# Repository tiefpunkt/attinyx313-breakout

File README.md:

# ATtiny x2313 Breakout Board

Want to try something out with an ATtiny2313 or 4313? Don't want to do it on a breadboard? Well, here you go.

This is a single sided board, with the schematics of [Alex Weber](http://tinkerlog.com/2009/01/18/attiny-breadboard-headers/)'s ATtiny breadboard adapter.

## Schematic

## Board

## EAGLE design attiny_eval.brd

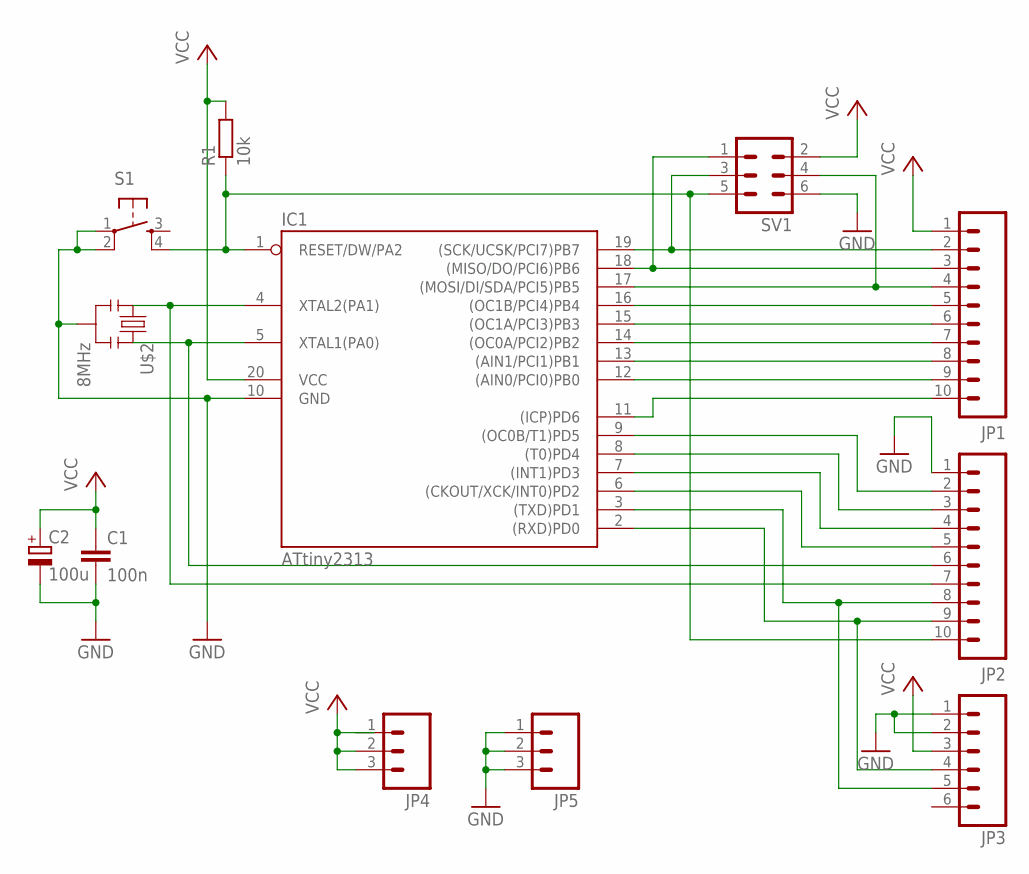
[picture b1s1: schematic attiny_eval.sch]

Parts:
C1: 100n; C025-025X050
C2: 100u; E2,5-5
IC1: ATtiny2313; DIL20
JP1, JP2: M100.1; 1X10
JP3: M06SIP; 1X06
JP4, JP5: M03PTH; 1X03
R1: 10k; 0207/10
S1: TAC_SWITCHPTH; TACTILE-PTH
SV1: MA03-2
U$2: 8MHz; RESONATOR-PTH

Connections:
GND: C1.2, C2.-, IC1.10 (GND), JP2.1, JP3.1, JP3.2, JP5.1, JP5.2, JP5.3, S1.1, S1.2, SV1.6, U$2.2
unnamed: IC1.4 (XTAL2(PA1)), JP2.7, U$2.1
unnamed: IC1.5 (XTAL1(PA0)), JP2.6, U$2.3
unnamed: IC1.1 (RESET/DW/PA2), JP2.10, R1.1, S1.4, SV1.5
unnamed: IC1.19 ((SCK/UCSK/PCI7)PB7), JP1.2, SV1.3
unnamed: IC1.18 ((MISO/DO/PCI6)PB6), JP1.3, SV1.1
unnamed: IC1.17 ((MOSI/DI/SDA/PCI5)PB5), JP1.4, SV1.4
unnamed: IC1.16 ((OC1B/PCI4)PB4), JP1.5
unnamed: IC1.15 ((OC1A/PCI3)PB3), JP1.6
unnamed: IC1.14 ((OC0A/PCI2)PB2), JP1.7
unnamed: IC1.13 ((AIN1/PCI1)PB1), JP1.8
unnamed: IC1.12 ((AIN0/PCI0)PB0), JP1.9
unnamed: IC1.11 ((ICP)PD6), JP1.10
unnamed: IC1.9 ((OC0B/T1)PD5), JP2.2
unnamed: IC1.8 ((T0)PD4), JP2.3
unnamed: IC1.7 ((INT1)PD3), JP2.4
unnamed: IC1.6 ((CKOUT/XCK/INT0)PD2), JP2.5
unnamed: IC1.3 ((TXD)PD1), JP2.8, JP3.5
RX: IC1.2 ((RXD)PD0), JP2.9, JP3.4
VCC: C1.1, C2.+, IC1.20 (VCC), JP1.1, JP3.3, JP4.1, JP4.2, JP4.3, R1.2, SV1.2

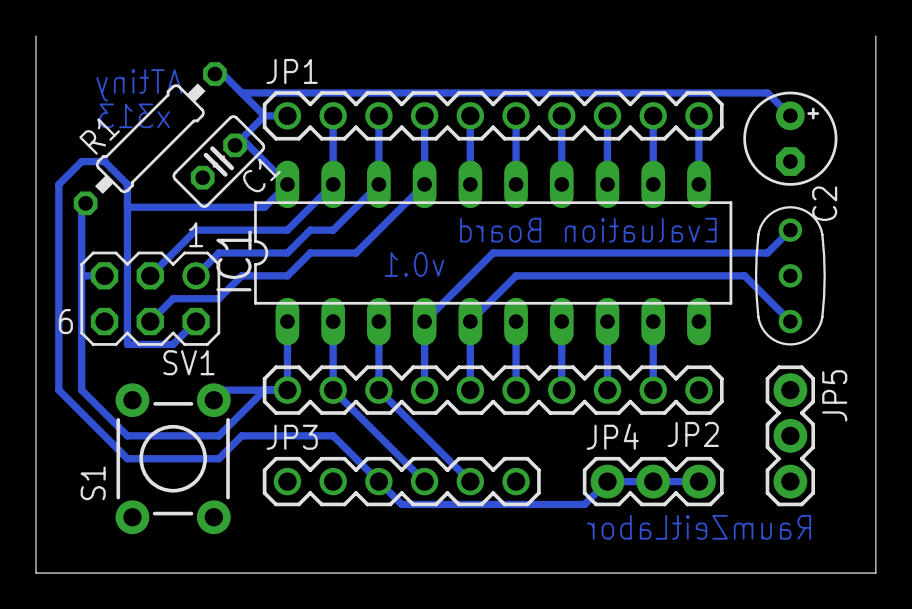
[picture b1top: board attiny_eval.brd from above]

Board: 2 copper layers, 46.7 x 29.8 mm, 12 parts (0 on the bottom side), 20 nets.

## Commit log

2013-03-19 rename
2013-03-19 solderpad support
2013-03-19 added readme

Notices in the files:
parts and their libraries:
SparkFun-Connectors: Licensing: CC v3.0 Share-Alike You are welcome to use this library for commercial purposes.
